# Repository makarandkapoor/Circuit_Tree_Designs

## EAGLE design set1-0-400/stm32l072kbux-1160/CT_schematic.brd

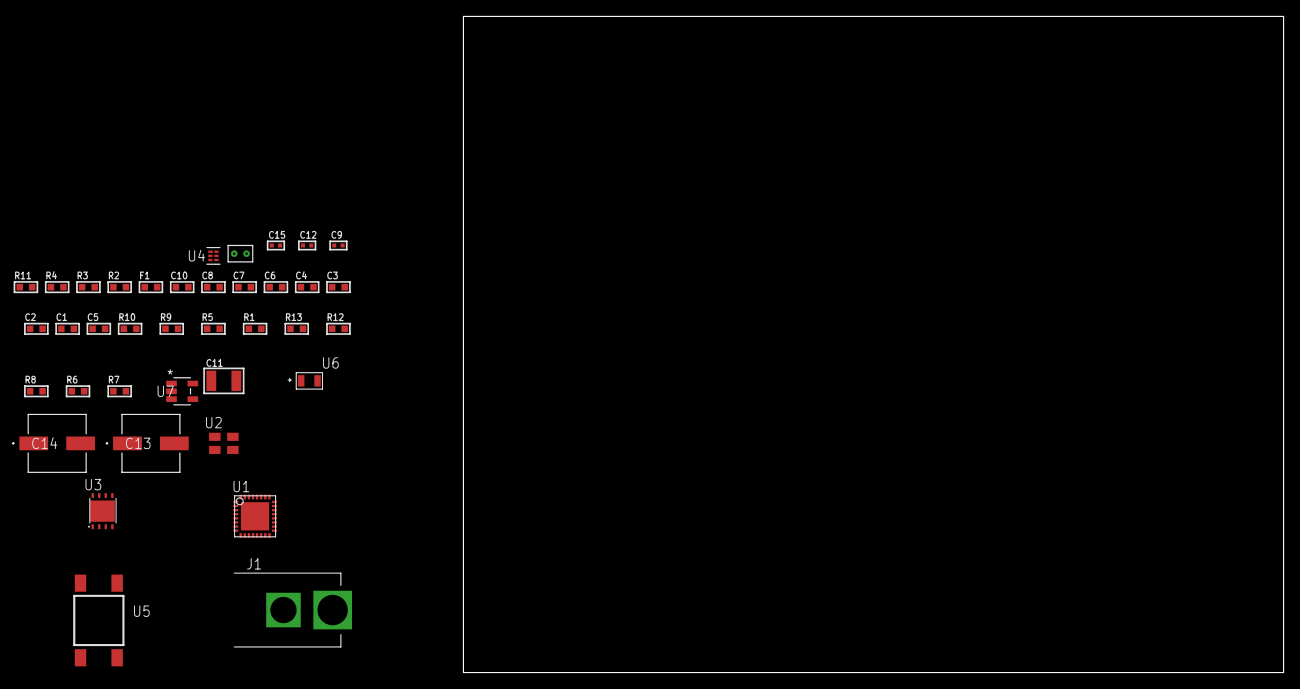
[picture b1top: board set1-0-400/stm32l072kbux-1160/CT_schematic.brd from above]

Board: 2 copper layers, 100.0 x 80.0 mm, 38 parts (0 on the bottom side), 16 nets, no tracks yet.

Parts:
C1, C2, C3, C4, C8: 1e-07; C0603
C5: 4.7e-06; C0603
C6: 1e-08; C0603
C7: 1e-06; C0603
C9, C15: 1e-08; C0402
C10: 8e-07; R0603
C11: 1e-05; C1210
C12: 1e-07; C0402
C13, C14: 0.0001; EXV-9H
F1: 240.0; L0603
J1: PJ-037B; PJ-037B_PACKAGE
R1, R5, R9, R10: 10000.0; R0603
R2: 1000.0; R0603
R3: 1600.5; R0603
R4: 4700.0; R0603
R6, R8: 100000.0; R0603
R7: 153694.38; R0603
R11: 9100.0; R0603
R12: 680000.0; R0603
R13: 120000.0; R0603
U1: STM32L072KBU6; UFQFPN32
U2: ASEK-32.768KHz-ECST; ASEK
U3: LP2951ACSDX/NOPB; WSON-8
U4: TPS3895ADRYR; SON-6
U5: 4-1437565-2; SW_4-1437565-2
U6: Q65110A2395; LGM67K-G1J2-24-Z
U7: nc7sz125m5x; NC7SZ125M5X
U8: Dummy; DUMMY_PACKAGE_78

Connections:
CLK_U1_1: U1.1, U2.3
GND: C1.2, C2.2, C3.2, C4.2, C5.2, C6.2, C7.2, C8.2, C9.2, C10.2, C11.2, C12.2, C13.2, C14.2, C15.2, J1.2, R2.2, R5.2, R8.2, R11.2, R13.2, U1.4, U1.16, U1.31, U1.EPAD, U2.2, U3.3, U3.4, U3.PAD, U4.2, U6.C, U7.1, U7.3, U8.1
NET_U1_3: R4.1, U1.3, U7.4
NET_U1_5: C6.1, C7.1, F1.1, U1.5
NET_U1_28: R3.1, U1.28, U6.A
NET_U1_29: R1.1, U1.29, U5.3, U5.4
NET_U1_30: R5.1, U1.30
NET_U3_5: R6.1, U3.5
NET_U3_7: R7.2, R8.1, U3.7
NET_U4_1: R10.1, R11.1, U4.1
NET_U4_3: R12.2, R13.1, U4.3
NET_U4_4: R9.1, U4.4, U7.2
NET_U5_1: R2.1, U5.1, U5.2
PROC_DAC_OUT2: U1.11, U8.2
VCC_S1_14V0: C10.1, C13.1, C14.1, J1.1, U3.8
VCC_TIER1_3V3: C1.1, C2.1, C3.1, C4.1, C5.1, C8.1, C9.1, C11.1, C12.1, C15.1, F1.2, R1.2, R3.2, R4.2, R6.2, R7.1, R9.2, R10.2, R12.1, U1.17, U1.24, U1.32, U2.4, U3.1, U4.6, U7.5

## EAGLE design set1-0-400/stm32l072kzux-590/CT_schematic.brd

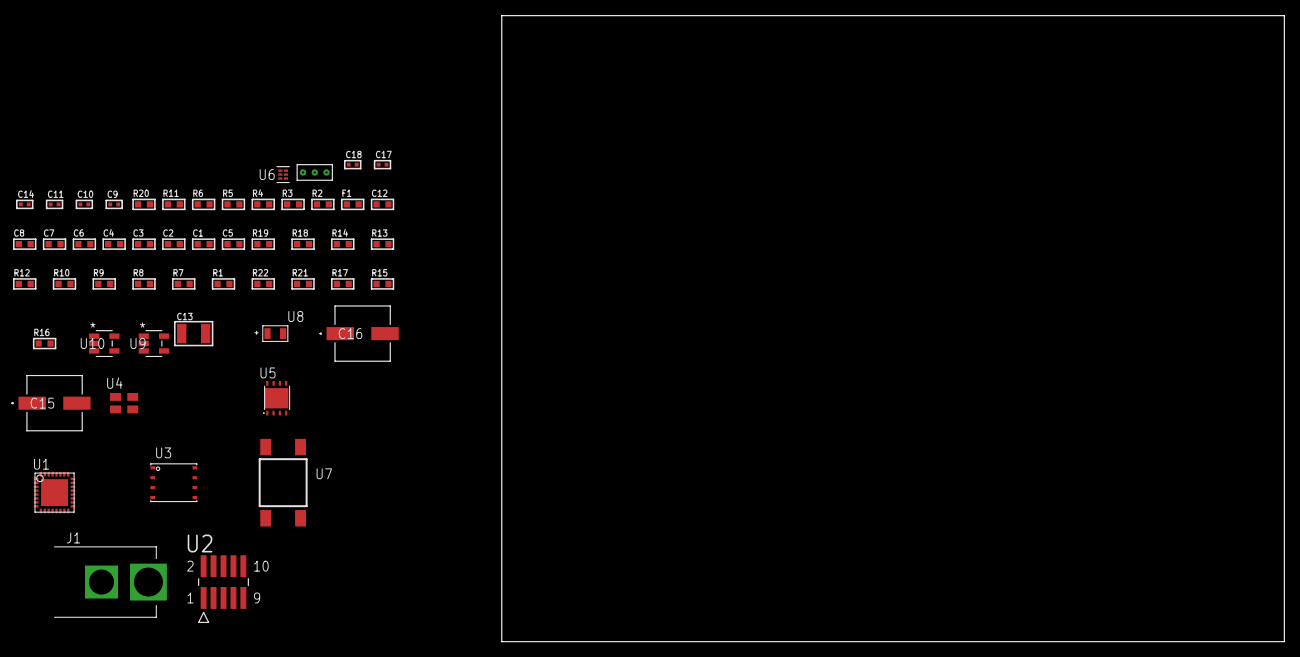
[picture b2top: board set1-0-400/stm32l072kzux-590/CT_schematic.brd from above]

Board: 2 copper layers, 100.0 x 80.0 mm, 53 parts (0 on the bottom side), 26 nets, no tracks yet.

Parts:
C1, C2, C3, C4, C8: 1e-07; C0603
C5: 4.7e-06; C0603
C6: 1e-08; C0603
C7, C12: 1e-06; C0603
C9, C14: 1e-07; C0402
C10, C11, C17, C18: 1e-08; C0402
C13: 1e-05; C1210
C15, C16: 0.0001; EXV-9H
F1: 240.0; L0603
J1: PJ-037B; PJ-037B_PACKAGE
R1, R7, R8, R9, R10, R12, R13, R14, R18, R19: 10000.0; R0603
R2: 1000.0; R0603
R3: 1600.5; R0603
R4: 4700.0; R0603
R5, R6: 2200.0; R0603
R11: 5.0; R0603
R15, R17: 100000.0; R0603
R16: 153694.38; R0603
R20: 9100.0; R0603
R21: 680000.0; R0603
R22: 120000.0; R0603
U1: STM32L072KZU6; UFQFPN32
U2: FTSH-105-01-L-DV-K; SAMTEC_FTSH-105-01-L-DV-K
U3: 24AA256-I/MF; DFN8-S
U4: ASEK-32.768KHz-ECST; ASEK
U5: LP2951ACSDX/NOPB; WSON-8
U6: TPS3895ADRYR; SON-6
U7: 4-1437565-2; SW_4-1437565-2
U8: Q65110A2395; LGM67K-G1J2-24-Z
U9, U10: nc7sz125m5x; NC7SZ125M5X
U11: Dummy; DUMMY_PACKAGE_114

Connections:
CLK_U1_1: U1.1, U4.3
GND: C1.2, C2.2, C3.2, C4.2, C5.2, C6.2, C7.2, C8.2, C9.2, C10.2, C11.2, C12.2, C13.2, C14.2, C15.2, C16.2, C17.2, C18.2, J1.2, R2.2, R7.2, R11.2, R12.2, R17.2, R20.2, R22.2, U1.4, U1.16, U1.31, U1.EPAD, U2.3, U2.5, U3.4, U3.7, U4.2, U5.3, U5.4, U5.PAD, U6.2, U8.C, U9.2, U9.3, U10.1, U10.3, U11.1
NET_U1_3: R4.1, U1.3, U10.4
NET_U1_5: C6.1, C7.1, F1.1, U1.5
NET_U1_19: R5.1, U1.19, U3.6
NET_U1_20: R6.1, U1.20, U3.5
NET_U1_28: R3.1, U1.28, U8.A
NET_U1_29: R1.1, U1.29, U7.3, U7.4
NET_U1_30: R7.1, U1.30
NET_U2_9: R11.1, U2.9
NET_U3_1: R12.1, U3.1
NET_U3_2: R13.1, U3.2
NET_U3_3: R14.1, U3.3
NET_U5_5: R15.1, U5.5
NET_U5_7: R16.2, R17.1, U5.7
NET_U6_1: R19.1, R20.1, U6.1
NET_U6_3: R21.2, R22.1, U6.3
NET_U6_4: R18.1, U6.4, U9.4, U10.2
NET_U7_1: R2.1, U7.1, U7.2
PROC_SYS_SWCLK: R9.1, U1.25, U2.4
PROC_SYS_SWDIO: R10.1, U1.23, U2.2
PROC_TIM2_CH1: U1.6, U11.3
PROC_TIM2_CH3: U1.8, U11.2
RST_OUT_U2_JTAG_RST_B: R8.1, U2.10, U9.1
VCC_S1_6V9: C12.1, C15.1, C16.1, J1.1, U5.8
VCC_TIER1_3V3: C1.1, C2.1, C3.1, C4.1, C5.1, C8.1, C9.1, C10.1, C11.1, C13.1, C14.1, C17.1, C18.1, F1.2, R1.2, R3.2, R4.2, R5.2, R6.2, R8.2, R9.2, R10.2, R13.2, R14.2, R15.2, R16.1, R18.2, R19.2, R21.1, U1.17, U1.24, U1.32, U2.1, U3.8, U4.4, U5.1, U6.6, U9.5, U10.5

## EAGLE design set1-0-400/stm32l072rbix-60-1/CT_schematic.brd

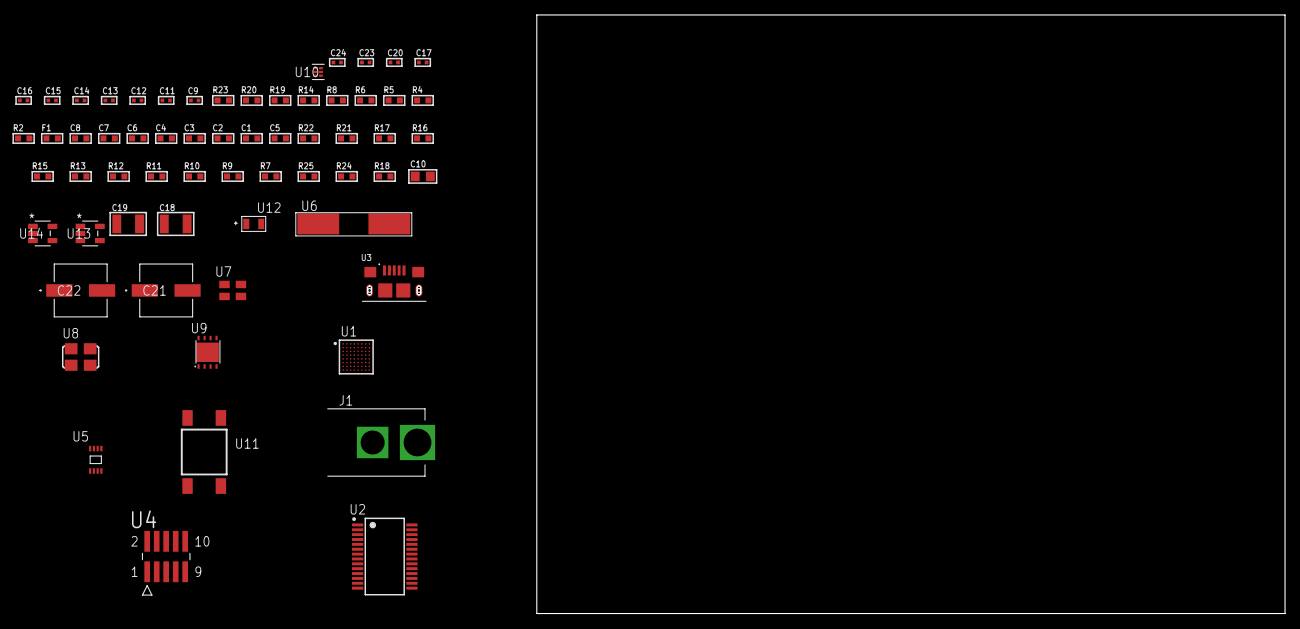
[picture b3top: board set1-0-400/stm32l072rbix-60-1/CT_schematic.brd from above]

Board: 2 copper layers, 122.6 x 80.0 mm, 63 parts (0 on the bottom side), 37 nets, no tracks yet.

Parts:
C1, C2, C3, C4, C8: 1e-07; C0603
C5: 4.7e-06; C0603
C6: 1e-08; C0603
C7: 1e-06; C0603
C9, C11, C12, C13, C20: 1e-07; C0402
C10: 4.7e-06; C0805
C14, C15, C16, C17, C23, C24: 1e-08; C0402
C18, C19: 1e-05; C1210
C21, C22: 0.0001; EXV-9H
F1: 240.0; L0603
J1: PJ-037B; PJ-037B_PACKAGE
R2, R20: 1000.0; R0603
R4, R8: 4700.0; R0603
R5, R6: 2200.0; R0603
R7, R9, R10, R11, R12, R13, R15, R16, R17, R21, R22: 10000.0; R0603
R14: 5.0; R0603
R18: 100000.0; R0603
R19: 2231.0; R0603
R23: 9100.0; R0603
R24: 680000.0; R0603
R25: 120000.0; R0603
U1: STM32L072RBI6; UFBGA64
U2: FT232RL-REEL; SSOP-28
U3: 10118193-0001LF; FCI_10118193-0001LF
U4: FTSH-105-01-L-DV-K; SAMTEC_FTSH-105-01-L-DV-K
U5: 24AA64T-I/MNY; TDFN-8/6MM
U6: ABLS-12.000MHZ-B4-T
U7: ASEK-32.768KHz-ECST; ASEK
U8: ASFL1-25MHZ-NCS; ASFL1
U9: LP3878SDX-ADJ/NOPB; WSON-8
U10: TPS3895ADRYR; SON-6
U11: 4-1437565-2; SW_4-1437565-2
U12: Q65110A2395; LGM67K-G1J2-24-Z
U13, U14: nc7sz125m5x; NC7SZ125M5X

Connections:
CLK_CRYSTAL_U2_27: U2.27, U6.1
CLK_CRYSTAL_U2_28: U2.28, U6.2
CLK_U1_A1: U1.A1, U7.3
CLK_U1_C1: U1.C1, U8.3
GND: C1.2, C2.2, C3.2, C4.2, C5.2, C6.2, C7.2, C8.2, C9.2, C10.2, C11.2, C12.2, C13.2, C14.2, C15.2, C16.2, C17.2, C18.2, C19.2, C20.2, C21.2, C22.2, C23.2, C24.2, J1.2, R2.2, R7.2, R10.2, R14.2, R15.2, R17.2, R20.2, R23.2, R25.2, U1.C2, U1.D4, U1.D5, U1.D6, U1.F1, U2.7, U2.18, U2.21, U2.25, U2.26, U3.5, U3.6, U3.7, U3.8, U3.9, U4.3, U4.5, U5.4, U7.2, U8.2, U9.3, U9.PAD, U10.2, U12.C, U13.2, U13.3, U14.1, U14.3
NET_U1_A3: R6.1, U1.A3, U5.5
NET_U1_B3: R5.1, U1.B3, U5.6
NET_U1_B4: R7.1, U1.B4
NET_U1_E1: R4.1, U1.E1, U14.4
NET_U1_H1: C6.1, C7.1, F1.1, U1.G1, U1.H1
NET_U1_H8: U11.3, U11.4
NET_U2_14: R9.1, U2.14
NET_U2_17: C11.1, U2.17
NET_U2_19: R10.1, U2.19
NET_U3_1: R8.1, U3.1
NET_U3_2: U2.16, U3.2
NET_U3_3: U2.15, U3.3
NET_U4_9: R14.1, U4.9
NET_U5_1: R15.1, U5.1
NET_U5_2: R16.1, U5.2
NET_U5_3: R17.1, U5.3
NET_U9_1: C17.1, U9.1
NET_U9_6: R19.2, R20.1, U9.6
NET_U9_8: R18.1, U9.8
NET_U10_1: R22.1, R23.1, U10.1
NET_U10_3: R24.2, R25.1, U10.3
NET_U10_4: R21.1, U10.4, U13.4, U14.2
NET_U11_1: R2.1, U11.1, U11.2
PROC_LPUART1_CTS: U1.G4, U2.3
PROC_LPUART1_RTS: U1.B5, U2.11
PROC_LPUART1_RX: U1.B6, U2.1
PROC_LPUART1_TX: U1.B7, U2.5
PROC_SYS_SWCLK: R12.1, U1.A7, U4.4
PROC_SYS_SWDIO: R13.1, U1.A8, U4.2
RST_OUT_U4_JTAG_RST_B: R11.1, U4.10, U13.1
VCC_S1_15V0: C18.1, C21.1, C22.1, J1.1, R18.2, U9.4
VCC_TIER1_3V3: C1.1, C2.1, C3.1, C4.1, C5.1, C8.1, C9.1, C10.1, C12.1, C13.1, C14.1, C15.1, C16.1, C19.1, C20.1, C23.1, C24.1, F1.2, R4.2, R5.2, R6.2, R9.2, R11.2, R12.2, R13.2, R16.2, R19.1, R21.2, R22.2, R24.1, U1.B2, U1.D2, U1.E4, U1.E5, U1.E6, U2.4, U2.20, U4.1, U5.7, U5.8, U7.4, U8.4, U9.5, U10.6, U13.5, U14.5

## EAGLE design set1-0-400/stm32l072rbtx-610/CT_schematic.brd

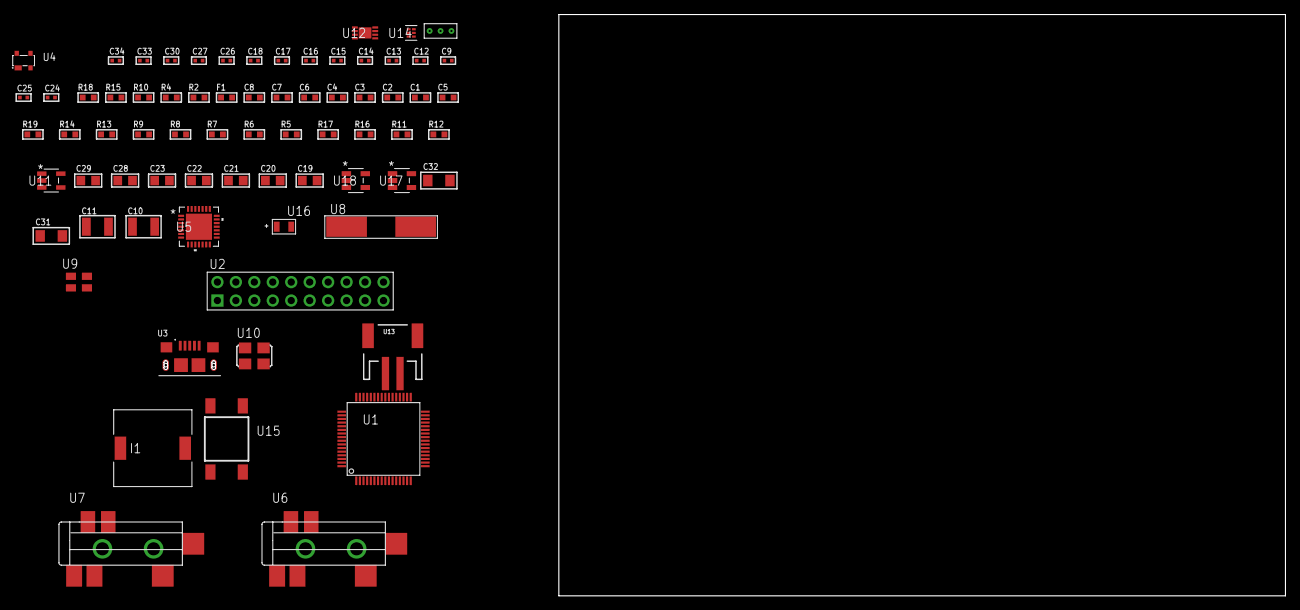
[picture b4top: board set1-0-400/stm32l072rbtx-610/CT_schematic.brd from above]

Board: 2 copper layers, 72 parts (0 on the bottom side), 35 nets, no tracks yet.

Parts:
C1, C2, C3, C4, C8: 1e-07; C0603
C5: 4.7e-06; C0603
C6: 1e-08; C0603
C7: 1e-06; C0603
C9, C14, C15, C16, C17, C18, C30: 1e-07; C0402
C10, C11: 2.2e-05; C1210
C12, C13: 1e-09; C0402
C19, C20, C21, C22, C23, C28, C29: 1e-05; C0805
C24, C25: 2.2e-11; C0402
C26, C27, C33, C34: 1e-08; C0402
C31, C32: 1e-05; C1206
F1: 240.0; L0603
I1: 5.2e-06; DR1040
R2: 1000.0; R0603
R4: 4700.0; R0603
R5, R6, R13, R14, R19: 10000.0; R0603
R7, R8, R9: 47000.0; R0603
R10: 680.0; R0603
R11: 220000.0; R0603
R12: 1000000.0; R0603
R15: 9100.0; R0603
R16: 680000.0; R0603
R17: 120000.0; R0603
R18: 2000.0; R0603
U1: STM32L072RBT6; LQFP64
U2: TST-110-05-T-D-RA
U3: 10118193-0001LF; FCI_10118193-0001LF
U4: prtr5v0u2ax; SOT143B
U5: WM8731CLSEFL; QFN-28
U6, U7: SJ-43515TS-SMT-TR
U8: ABLS-12.288MHZ-B4-T
U9: ASEK-32.768KHz-ECST; ASEK
U10: ASFL1-25MHZ-NCS; ASFL1
U11: ltc3406es5; TSOT-23-5
U12: MCP73831T-2ACI/MC; DFN8_2X3MC
U13: S2B-PH-SM4-TB(LF)(SN); JST-2-SMD
U14: TPS3895ADRYR; SON-6
U15: 4-1437565-2; SW_4-1437565-2
U16: Q65110A2395; LGM67K-G1J2-24-Z
U17, U18: nc7sz125m5x; NC7SZ125M5X
U19: Dummy; DUMMY_PACKAGE_155

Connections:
CLK_CRYSTAL_U5_1: C24.1, U5.1, U8.1
CLK_CRYSTAL_U5_2: C25.1, U5.2, U8.2
CLK_U1_3: U1.3, U9.3
CLK_U1_5: U1.5, U10.3
GND: C1.2, C2.2, C3.2, C4.2, C5.2, C6.2, C7.2, C8.2, C9.2, C13.2, C14.2, C15.2, C16.2, C17.2, C18.2, C19.2, C20.2, C21.2, C22.2, C23.2, C24.2, C25.2, C26.2, C27.2, C28.2, C29.1, C29.2, C30.2, C31.2, C32.2, C33.2, C34.2, R2.2, R5.2, R7.2, R8.2, R9.2, R11.2, R15.2, R17.2, R18.2, U1.12, U1.18, U1.31, U1.47, U1.63, U2.4, U2.6, U2.8, U2.10, U2.12, U2.14, U2.16, U2.18, U2.20, U3.5, U3.6, U3.7, U3.8, U3.9, U4.1, U5.4, U5.15, U5.19, U5.25, U5.26, U5.29, U6.1, U7.1, U9.2, U10.2, U11.2, U12.6, U12.9, U13.2, U14.2, U16.C, U17.2, U17.3, U18.1, U18.3, U19.1
INPUT_USBPOWER_5V: C31.1, R19.2, U3.1, U4.4, U12.1, U12.2
NET_U1_7: R4.1, U1.7, U18.4
NET_U1_13: C6.1, C7.1, F1.1, U1.13
NET_U1_60: R5.1, U1.60
NET_U1_62: U15.3, U15.4
NET_U5_20: C18.1, C23.1, U5.20
NET_U6_2: C11.1, R8.1, U6.2
NET_U6_5: C10.1, R7.1, U6.5
NET_U7_5: C12.1, C13.1, R9.1, R10.1, U7.5
NET_U11_3: I1.1, U11.3
NET_U11_5: R11.1, R12.1, U11.5
NET_U11_ATNET_3: I1.2, R12.2
NET_U12_5: R19.1, U12.5
NET_U12_8: R18.1, U12.8
NET_U14_1: R14.1, R15.1, U14.1
NET_U14_3: R16.2, R17.1, U14.3
NET_U14_4: R13.1, U14.4, U17.4, U18.2
NET_U15_1: R2.1, U15.1, U15.2
PROC_I2S2_CK: U1.34, U5.7
PROC_I2S2_SD: U1.11, U5.8
PROC_I2S2_WS: U1.33, U5.9, U5.11
PROC_SYS_SWCLK: U1.49, U2.9
PROC_SYS_SWDIO: U1.46, U2.7
PROC_TIM2_CH1: U1.14, U19.3
PROC_TIM2_CH3: U1.16, U19.2
PROC_USB_DM: U1.44, U3.2, U4.3
PROC_USB_DP: U1.45, U3.3, U4.2
RST_OUT_U2_SRESET_B: R6.1, U2.15, U17.1
VCC_S1_3V7: C28.1, C32.1, U11.4, U12.3, U12.4, U13.1
VCC_TIER1_3V3: C1.1, C2.1, C3.1, C4.1, C5.1, C8.1, C9.1, C14.1, C15.1, C16.1, C17.1, C19.1, C20.1, C21.1, C22.1, C26.1, C27.1, C29.2, C30.1, C33.1, C34.1, F1.2, I1.2, R4.2, R6.2, R12.2, R13.2, R14.2, R16.1, U1.1, U1.19, U1.32, U1.48, U1.64, U2.1, U5.3, U5.5, U5.12, U5.18, U9.4, U10.4, U14.6, U17.5, U18.5

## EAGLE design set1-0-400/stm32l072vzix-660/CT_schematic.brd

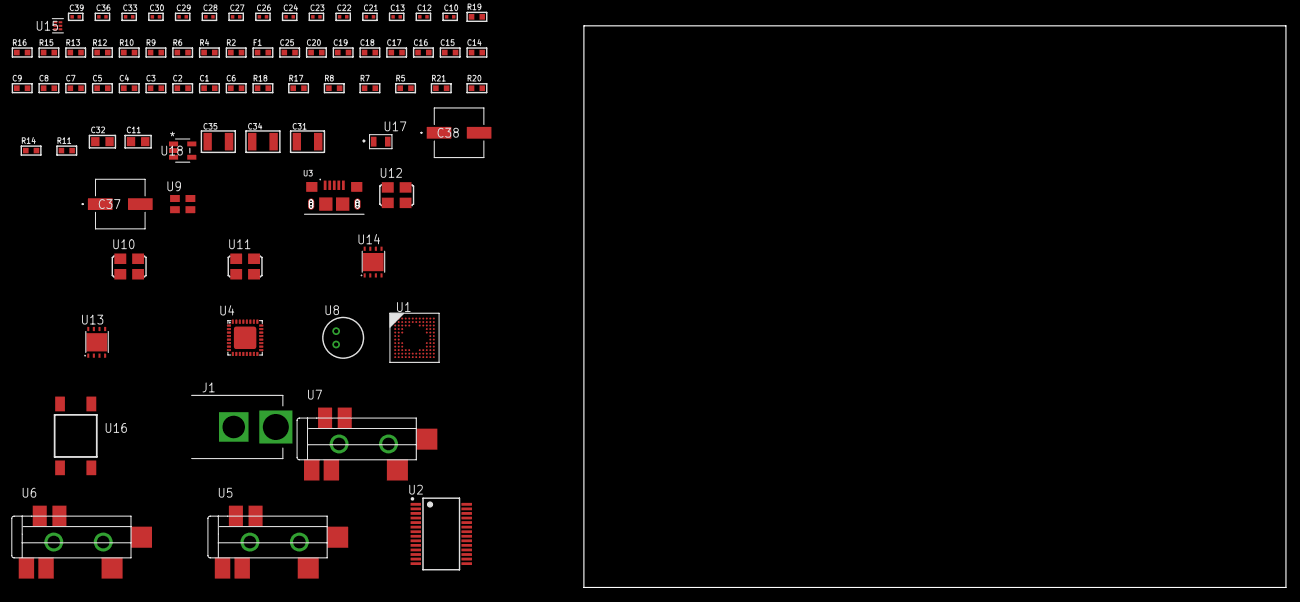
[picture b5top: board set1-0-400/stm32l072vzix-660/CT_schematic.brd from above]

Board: 2 copper layers, 78 parts (0 on the bottom side), 48 nets, no tracks yet.

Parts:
C1, C2, C3, C4, C5, C9: 1e-07; C0603
C6: 4.7e-06; C0603
C7: 1e-08; C0603
C8, C14, C15, C16, C17, C18, C19, C20, C25: 1e-06; C0603
C10, C12, C13, C21, C22, C23, C24, C36: 1e-07; C0402
C11: 4.7e-06; C0805
C26, C27, C28, C29, C30, C33, C39: 1e-08; C0402
C31, C34, C35: 1e-05; C1210
C32: 1e-05; C0805
C37, C38: 0.0001; EXV-9H
F1: 240.0; L0603
J1: PJ-037B; PJ-037B_PACKAGE
R2, R13, R16: 1000.0; R0603
R4, R6: 4700.0; R0603
R5, R7, R8, R17, R18: 10000.0; R0603
R9, R10: 1270.0; R0603
R11, R14: 100000.0; R0603
R12: 200.0; R0603
R15: 2231.0; R0603
R19: 9100.0; R0603
R20: 680000.0; R0603
R21: 120000.0; R0603
U1: STM32L072VZI6; UFBGA100
U2: FT232RL-REEL; SSOP-28
U3: 10118193-0001LF; FCI_10118193-0001LF
U4: SGTL5000XNAA3; QFN-32
U5, U6, U7: SJ-43515TS-SMT-TR
U8: WM-64PCT; WM-64PC
U9: ASEK-32.768KHz-ECST; ASEK
U10: ASFL1-12MHZ-NCS; ASFL1
U11: ASFL-24.57MHZ-NCS; ASFL1
U12: ASFL1-25MHZ-NCS; ASFL1
U13, U14: LP3878SDX-ADJ/NOPB; WSON-8
U15: TPS3895ADRYR; SON-6
U16: 4-1437565-2; SW_4-1437565-2
U17: Q65110A2395; LGM67K-G1J2-24-Z
U18: nc7sz125m5x; NC7SZ125M5X

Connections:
CLK_U1_D1: U1.D1, U9.3
CLK_U1_F1: U1.F1, U12.3
CLK_U2_27: U2.27, U10.3
CLK_U4_21: U4.21, U11.3
GND: C1.2, C2.2, C3.2, C4.2, C5.2, C6.2, C7.2, C8.2, C9.2, C10.2, C11.2, C12.2, C13.2, C21.2, C22.2, C23.2, C24.2, C25.2, C26.2, C27.2, C28.2, C29.2, C30.2, C31.2, C32.2, C33.2, C34.2, C35.2, C36.2, C37.2, C38.2, C39.2, J1.2, R2.2, R5.2, R8.2, R10.2, R13.2, R16.2, R19.2, R21.2, U1.D3, U1.E3, U1.F11, U1.F12, U1.J1, U1.K1, U2.7, U2.18, U2.21, U2.25, U2.26, U3.5, U3.6, U3.7, U3.8, U3.9, U4.1, U4.3, U4.7, U4.EXP, U6.1, U7.1, U8.2, U9.2, U10.2, U11.2, U12.2, U13.3, U13.PAD, U14.3, U14.PAD, U15.2, U17.C, U18.1, U18.3
NET_U1_A4: R5.1, U1.A4
NET_U1_H2: R4.1, U1.H2, U18.4
NET_U1_M1: C7.1, C8.1, F1.1, U1.L1, U1.M1
NET_U1_M12: U16.3, U16.4
NET_U2_14: R7.1, U2.14
NET_U2_17: C12.1, U2.17
NET_U2_19: R8.1, U2.19
NET_U3_1: R6.1, U3.1
NET_U3_2: U2.16, U3.2
NET_U3_3: U2.15, U3.3
NET_U4_10: C24.1, U4.10
NET_U4_29: R9.1, U4.29
NET_U4_31: R10.1, U4.31
NET_U5_1: U4.4, U5.1
NET_U5_2: U4.2, U5.2
NET_U5_5: U4.6, U5.5
NET_U6_2: C15.1, U6.2
NET_U6_5: C14.1, U6.5
NET_U7_2: C17.1, C18.1, U7.2
NET_U7_5: C16.1, U7.5
NET_U7_13: C17.2, C18.2
NET_U8_1: C19.1, C20.1, C25.1, U4.16, U8.1
NET_U8_15: C19.2, C20.2
NET_U13_1: C30.1, U13.1
NET_U13_6: R12.2, R13.1, U13.6
NET_U13_8: R11.1, U13.8
NET_U14_1: C33.1, U14.1
NET_U14_6: R15.2, R16.1, U14.6
NET_U14_8: R14.1, U14.8
NET_U15_1: R18.1, R19.1, U15.1
NET_U15_3: R20.2, R21.1, U15.3
NET_U15_4: R17.1, U15.4, U18.2
NET_U16_1: R2.1, U16.1, U16.2
PROC_I2S2_CK: U1.B9, U4.24
PROC_I2S2_SD: U1.B7, U4.26
PROC_I2S2_WS: U1.B3, U4.23
PROC_LPUART1_CTS: U1.J11, U2.3
PROC_LPUART1_RTS: U1.C8, U2.11
PROC_LPUART1_RX: U1.A11, U2.1
PROC_LPUART1_TX: U1.A10, U2.5
VCC_S1_11V7: C31.1, C34.1, C37.1, C38.1, J1.1, R11.2, R14.2, U13.4, U14.4
VCC_TIER1_1V2: C21.1, C32.1, R12.1, U4.30, U13.5
VCC_TIER1_3V3: C1.1, C2.1, C3.1, C4.1, C5.1, C6.1, C9.1, C10.1, C11.1, C13.1, C22.1, C23.1, C26.1, C27.1, C28.1, C29.1, C35.1, C36.1, C39.1, F1.2, R4.2, R7.2, R9.2, R15.1, R17.2, R18.2, R20.1, U1.C4, U1.C11, U1.E2, U1.G11, U1.G12, U1.H3, U2.4, U2.20, U4.5, U4.20, U9.4, U10.4, U11.4, U12.4, U14.5, U15.6, U18.5

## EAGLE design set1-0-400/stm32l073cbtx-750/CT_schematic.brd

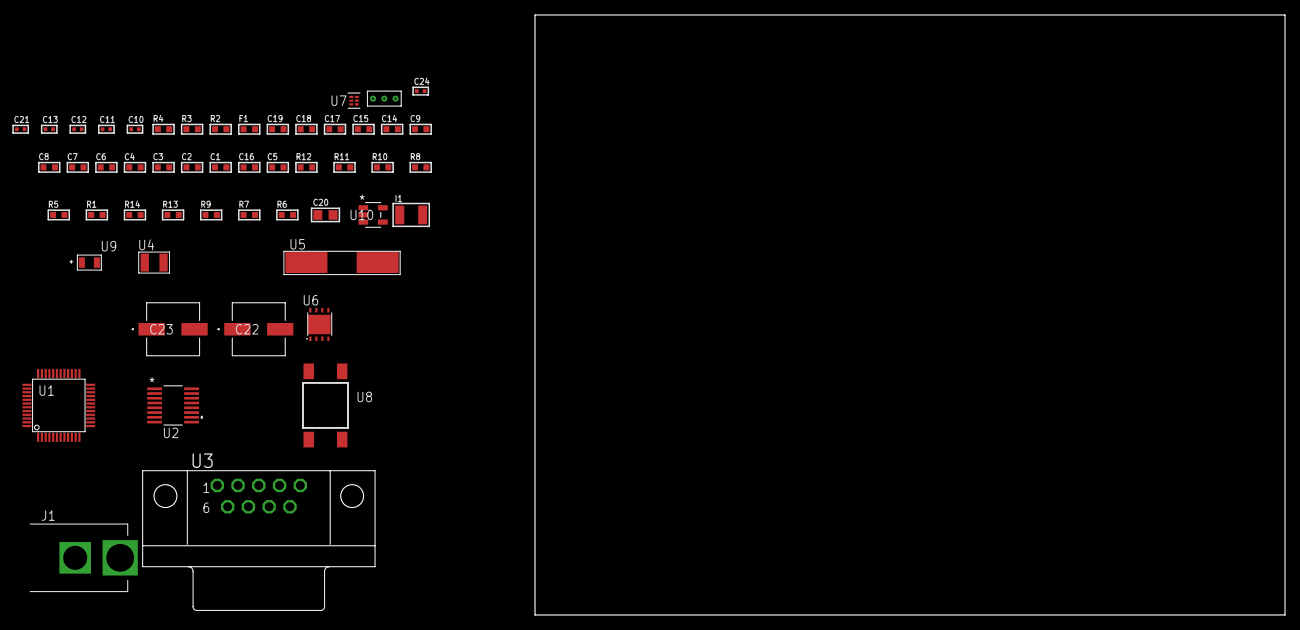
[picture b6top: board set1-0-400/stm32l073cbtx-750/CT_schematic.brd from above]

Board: 2 copper layers, 100.0 x 80.0 mm, 52 parts (0 on the bottom side), 34 nets, no tracks yet.

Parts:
C1, C2, C3, C4, C6, C9: 1e-07; C0603
C5: 4.7e-06; C0603
C7: 1e-08; C0603
C8, C14, C15, C17, C18, C19: 1e-06; C0603
C10, C11, C12, C13: 1e-11; C0402
C16: 2.2e-07; C0603
C20: 1e-05; C0805
C21: 1e-07; C0402
C22, C23: 0.0001; EXV-9H
C24: 1e-08; C0402
F1: 240.0; L0603
I1: 1e-05; L1210
J1: PJ-037B; PJ-037B_PACKAGE
R1, R5, R10, R11: 10000.0; R0603
R2: 1000.0; R0603
R3: 910.0; R0603
R4: 4700.0; R0603
R6, R7, R9: 100000.0; R0603
R8: 36000.0; R0603
R12: 82000.0; R0603
R13: 300000.0; R0603
R14: 120000.0; R0603
U1: STM32L073CBT6; LQFP48
U2: LTC2804CGN-1#PBF; SSOP-16
U3: 182-009-113R531; 182-009-MALE
U4: ABS07-32.768KHZ-7-T
U5: ABLS-25.000MHZ-B2F-T
U6: LP2951ACSDX/NOPB; WSON-8
U7: TPS3895ADRYR; SON-6
U8: 4-1437565-2; SW_4-1437565-2
U9: Q65110A2395; LGM67K-G1J2-24-Z
U10: nc7sz125m5x; NC7SZ125M5X
U11: Dummy; DUMMY_PACKAGE_103

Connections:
CLK_CRYSTAL_U1_3: C10.1, U1.3, U4.1
CLK_CRYSTAL_U1_4: C11.1, U1.4, U4.2
CLK_CRYSTAL_U1_5: C12.1, U1.5, U5.1
CLK_CRYSTAL_U1_6: C13.1, U1.6, U5.2
GND: C1.2, C2.2, C3.2, C4.2, C5.2, C6.2, C7.2, C8.2, C9.2, C10.2, C11.2, C12.2, C13.2, C14.2, C15.2, C17.2, C18.2, C19.2, C20.2, C21.2, C22.2, C23.2, C24.2, J1.2, R2.2, R5.2, R9.2, R12.2, R14.2, U1.8, U1.23, U1.35, U1.47, U2.8, U3.5, U6.3, U6.4, U6.PAD, U7.2, U9.C, U10.1, U10.3, U11.1
NET_U1_1: C6.1, U1.1
NET_U1_7: R4.1, U1.7, U10.4
NET_U1_9: C7.1, C8.1, F1.1, U1.9
NET_U1_44: R5.1, U1.44
NET_U1_45: R3.1, U1.45, U9.A
NET_U1_46: R1.1, U1.46, U8.3, U8.4
NET_U2_6: C14.1, U2.6
NET_U2_7: C16.1, I1.2, U2.7
NET_U2_9: C15.1, U2.9
NET_U2_10: C16.2, U2.10
NET_U2_11: R6.1, U2.11
NET_U3_2: U2.1, U3.2
NET_U3_3: U2.3, U3.3
NET_U3_7: U2.2, U3.7
NET_U3_8: U2.4, U3.8
NET_U6_5: R7.1, U6.5
NET_U6_7: R8.2, R9.1, U6.7
NET_U7_1: R11.1, R12.1, U7.1
NET_U7_3: R13.2, R14.1, U7.3
NET_U7_4: R10.1, U7.4, U10.2
NET_U8_1: R2.1, U8.1, U8.2
PROC_ADC_IN1: U1.11, U11.3
PROC_ADC_IN4: U1.14, U11.2
PROC_LPUART1_CTS: U1.16, U2.13
PROC_LPUART1_RTS: U1.19, U2.15
PROC_LPUART1_RX: U1.13, U2.16
PROC_LPUART1_TX: U1.12, U2.14
VCC_S1_9V5: C19.1, C22.1, C23.1, J1.1, U6.8
VCC_TIER1_1V8: C1.1, C2.1, C3.1, C4.1, C5.1, C9.1, C17.1, C18.1, C20.1, C21.1, C24.1, F1.2, I1.1, R1.2, R3.2, R4.2, R6.2, R7.2, R8.1, R10.2, R11.2, R13.1, U1.24, U1.36, U1.48, U2.5, U2.12, U6.1, U7.6, U10.5

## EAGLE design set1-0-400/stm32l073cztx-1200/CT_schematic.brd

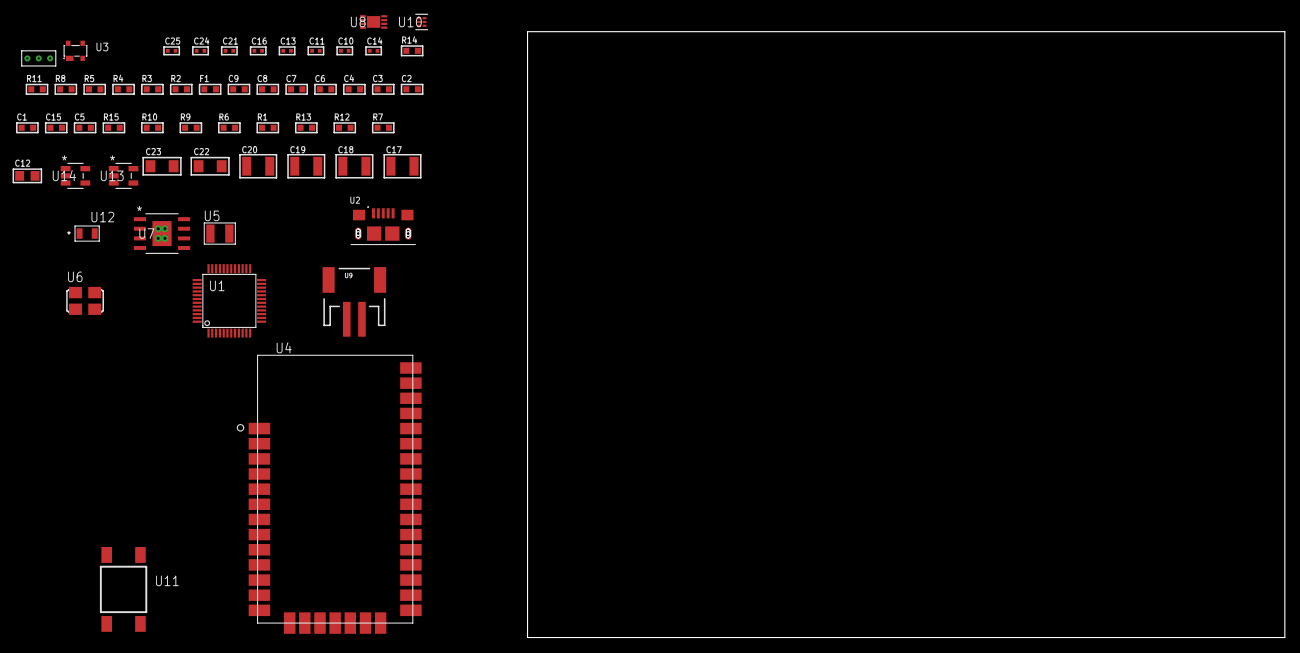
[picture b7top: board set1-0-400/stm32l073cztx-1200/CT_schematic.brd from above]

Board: 2 copper layers, 122.6 x 80.0 mm, 56 parts (0 on the bottom side), 29 nets, no tracks yet.

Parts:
C1, C2, C3, C4, C6, C9: 1e-07; C0603
C5: 4.7e-06; C0603
C7: 1e-08; C0603
C8: 1e-06; C0603
C10, C11: 1e-11; C0402
C12: 1e-05; C0805
C13, C21: 1e-07; C0402
C14: 4.7e-11; C0402
C15: 8.2e-12; C0603
C16, C24, C25: 1e-08; C0402
C17, C18, C19, C20: 1e-05; C1210
C22, C23: 1e-05; C1206
F1: 240.0; L0603
R1, R6, R9, R10, R15: 10000.0; R0603
R2: 1000.0; R0603
R3: 1600.5; R0603
R4, R5: 4700.0; R0603
R7: 4031.5447154472; R0603
R8: 2200.0; R0603
R11: 9100.0; R0603
R12: 680000.0; R0603
R13: 120000.0; R0603
R14: 2000.0; R0603
U1: STM32L073CZT6; LQFP48
U2: 10118193-0001LF; FCI_10118193-0001LF
U3: prtr5v0u2ax; SOT143B
U4: XB24CZ7UIS-004
U5: ABS07-32.768KHZ-7-T
U6: ASFL1-25MHZ-NCS; ASFL1
U7: MIC5234YME; SOIC-8_EP
U8: MCP73831T-2ACI/MC; DFN8_2X3MC
U9: S2B-PH-SM4-TB(LF)(SN); JST-2-SMD
U10: TPS3895ADRYR; SON-6
U11: 4-1437565-2; SW_4-1437565-2
U12: Q65110A2395; LGM67K-G1J2-24-Z
U13, U14: nc7sz125m5x; NC7SZ125M5X
U15: Dummy; DUMMY_PACKAGE_116

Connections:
CLK_CRYSTAL_U1_3: C10.1, U1.3, U5.1
CLK_CRYSTAL_U1_4: C11.1, U1.4, U5.2
CLK_U1_5: U1.5, U6.3
GND: C1.2, C2.2, C3.2, C4.2, C5.2, C6.2, C7.2, C8.2, C9.2, C10.2, C11.2, C12.2, C13.2, C14.2, C15.2, C16.2, C17.2, C18.2, C19.2, C20.2, C21.2, C22.2, C23.2, C24.2, C25.2, R2.2, R6.2, R8.2, R11.2, R13.2, R14.2, U1.8, U1.23, U1.35, U1.47, U2.5, U2.6, U2.7, U2.8, U2.9, U3.1, U4.1, U4.11, U4.13, U4.22, U4.35, U6.2, U7.7, U7.EPAD, U8.6, U8.9, U9.2, U10.2, U12.C, U13.1, U13.3, U14.1, U14.3, U15.1
INPUT_USBPOWER_5V: C22.1, R15.2, U2.1, U3.4, U8.1, U8.2
NET_U1_1: C6.1, U1.1
NET_U1_7: R5.1, U1.7, U14.4
NET_U1_9: C7.1, C8.1, F1.1, U1.9
NET_U1_44: R6.1, U1.44
NET_U1_45: R3.1, U1.45, U12.A
NET_U1_46: R1.1, U1.46, U11.3, U11.4
NET_U4_6: R4.1, U4.6, U13.4
NET_U7_4: R7.2, R8.1, U7.4
NET_U8_5: R15.1, U8.5
NET_U8_8: R14.1, U8.8
NET_U10_1: R10.1, R11.1, U10.1
NET_U10_3: R12.2, R13.1, U10.3
NET_U10_4: R9.1, U10.4, U13.2, U14.2
NET_U11_1: R2.1, U11.1, U11.2
PROC_ADC_IN3: U1.13, U15.2
PROC_ADC_IN9: U1.19, U15.3
PROC_SPI1_MISO: U1.16, U4.17
PROC_SPI1_MOSI: U1.17, U4.16
PROC_SPI1_NSS: U1.14, U4.15
PROC_SPI1_SCK: U1.15, U4.14
PROC_USB_DM: U1.32, U2.2, U3.3
PROC_USB_DP: U1.33, U2.3, U3.2
VCC_S1_3V7: C17.1, C18.1, C23.1, U7.5, U7.8, U8.3, U8.4, U9.1
VCC_TIER1_3V3: C1.1, C2.1, C3.1, C4.1, C5.1, C9.1, C12.1, C13.1, C14.1, C15.1, C16.1, C19.1, C20.1, C21.1, C24.1, C25.1, F1.2, R1.2, R3.2, R4.2, R5.2, R7.1, R9.2, R10.2, R12.1, U1.24, U1.36, U1.48, U4.2, U4.27, U6.4, U7.1, U10.6, U13.5, U14.5
